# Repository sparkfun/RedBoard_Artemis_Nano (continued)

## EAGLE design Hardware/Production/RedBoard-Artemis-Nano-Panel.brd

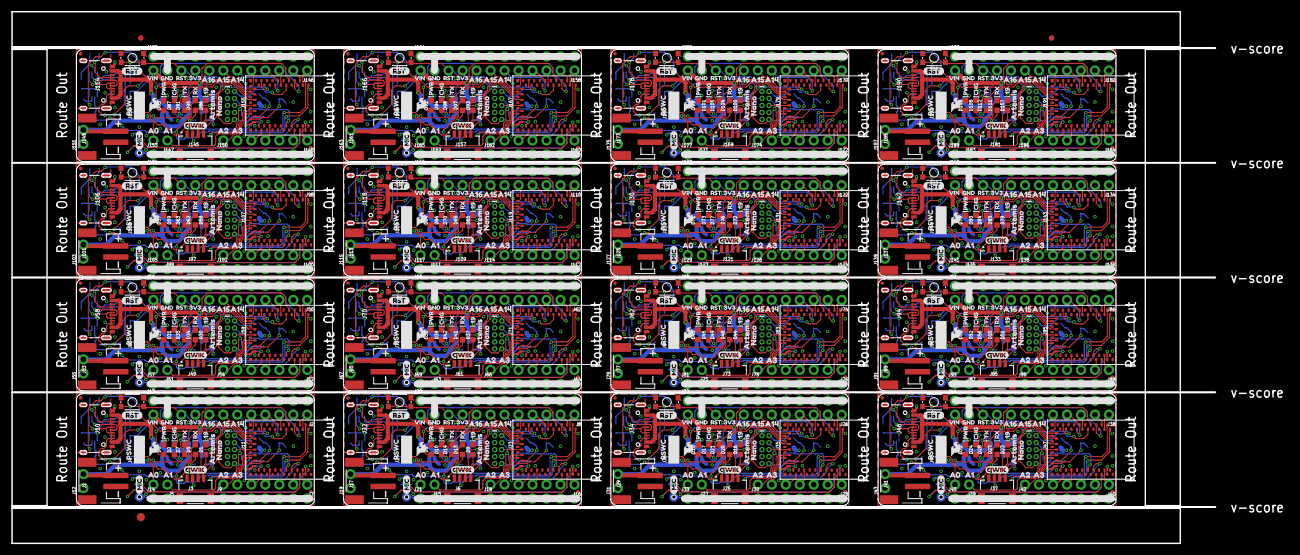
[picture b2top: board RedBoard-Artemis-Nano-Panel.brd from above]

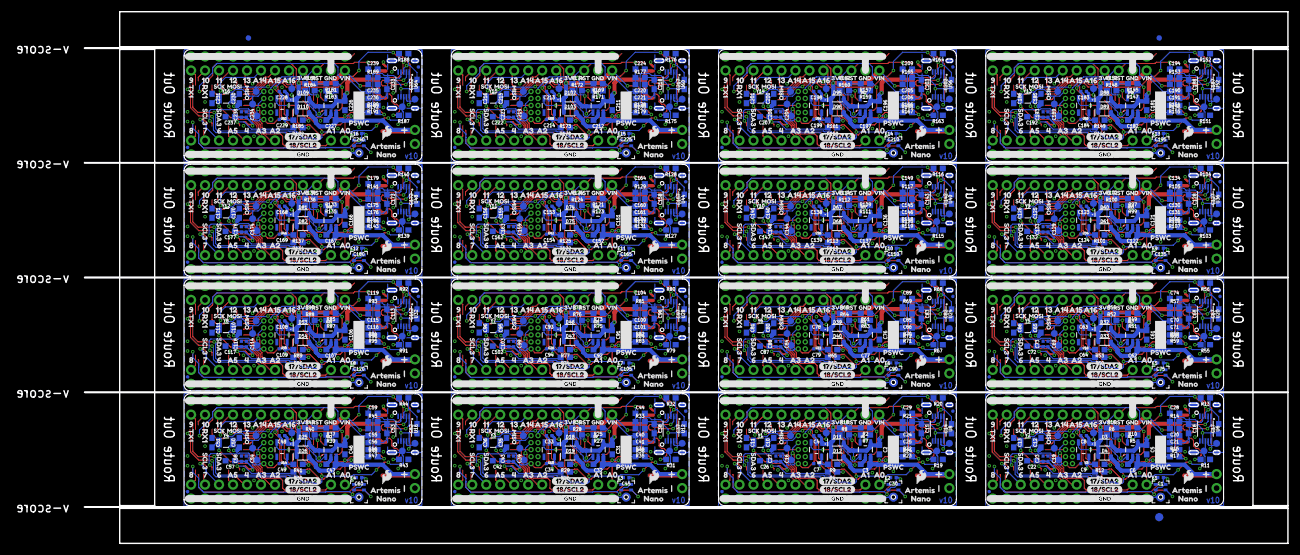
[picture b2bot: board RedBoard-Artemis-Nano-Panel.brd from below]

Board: 4 copper layers, 218.4 x 96.5 mm, 1990 parts (1267 on the bottom side), 784 nets.

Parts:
C1, C16, C19, C30, C39, C45, C54, C60, C69, C75, C84, C90, C99, C105, C114, C120, C129, C135, C144, C150, C159, C165, C174, C180, C189, C195, C204, C210, C219, C225, C234, C240: 0.1uF; 0402-TIGHT
C2, C3, C5, C6, C31, C32, C46, C47, C61, C62, C76, C77, C91, C92, C106, C107, C121, C122, C136, C137, C151, C152, C166, C167, C181, C182, C196, C197, C211, C212, C226, C227: 4.7uF; 0603
C4, C7, C8, C9, C23, C27, C33, C34, C43, C48, C49, C58, C63, C64, C73, C78, C79, C88, C93, C94, C103, C108, C109, C118, C123, C124, C133, C138, C139, C148, C153, C154, C163, C168, C169, C178, C183, C184, C193, C198, C199, C208, C213, C214, C223, C228, C229, C238: 1.0uF; 0402-TIGHT
C10, C11, C12, C13, C35, C36, C50, C51, C65, C66, C80, C81, C95, C96, C110, C111, C125, C126, C140, C141, C155, C156, C170, C171, C185, C186, C200, C201, C215, C216, C230, C231: 15pF; 0603
C14, C17, C37, C52, C67, C82, C97, C112, C127, C142, C157, C172, C187, C202, C217, C232: 10nF; 0603
C15, C18, C20, C21, C24, C25, C38, C40, C41, C53, C55, C56, C68, C70, C71, C83, C85, C86, C98, C100, C101, C113, C115, C116, C128, C130, C131, C143, C145, C146, C158, C160, C161, C173, C175, C176, C188, C190, C191, C203, C205, C206, C218, C220, C221, C233, C235, C236: 0.1uF; 0603
C22, C26, C42, C57, C72, C87, C102, C117, C132, C147, C162, C177, C192, C207, C222, C237: 10uF; 0603
C28, C29, C44, C59, C74, C89, C104, C119, C134, C149, C164, C179, C194, C209, C224, C239: 1nF; 0603
D1, D9, D16, D23, D30, D37, D44, D51, D58, D65, D72, D79, D86, D93, D100, D107: BLUE; LED-0603
D2, D5, D10, D13, D17, D20, D24, D27, D31, D34, D38, D41, D45, D48, D52, D55, D59, D62, D66, D69, D73, D76, D80, D83, D87, D90, D94, D97, D101, D104, D108, D111: Yellow; LED-0603
D3, D4, D11, D12, D18, D19, D25, D26, D32, D33, D39, D40, D46, D47, D53, D54, D60, D61, D67, D68, D74, D75, D81, D82, D88, D89, D95, D96, D102, D103, D109, D110: 1A/23V/620mV; SOD-323
D6, D8, D15, D22, D29, D36, D43, D50, D57, D64, D71, D78, D85, D92, D99, D106: RED; LED-0603
D7, D14, D21, D28, D35, D42, D49, D56, D63, D70, D77, D84, D91, D98, D105, D112: GREEN; LED-0603
E1, E2, E3, E4, E5, E6, E7, E8, E9, E10, E11, E12, E13, E14, E15, E16: SPH0641LM4H; SPH0641LM4H-1_MICROPHONE
E$1, E$2, E$3, E$4: FIDUCIAL-1X2
E$5, E$6: FIDUCIAL-1.5X3
FD1, FD2, FD3, FD4, FD5, FD6, FD7, FD8, FD9, FD10, FD11, FD12, FD13, FD14, FD15, FD16, FD17, FD18, FD19, FD20, FD21, FD22, FD23, FD24, FD25, FD26, FD27, FD28, FD29, FD30, FD31, FD32, FD33, FD34, FD35, FD36, FD37, FD38, FD39, FD40, FD41, FD42, FD43, FD44, FD45, FD46, FD47, FD48, FD49, FD50, FD51, FD52, FD53, FD54, FD55, FD56, FD57, FD58, FD59, FD60, FD61, FD62, FD63, FD64: FIDUCIALUFIDUCIAL; FIDUCIAL-MICRO
FRAME1, FRAME2, FRAME3, FRAME4, FRAME5, FRAME6, FRAME7, FRAME8, FRAME9, FRAME10, FRAME11, FRAME12, FRAME13, FRAME14, FRAME15, FRAME16: FRAME-LETTERNO_PACKAGE; DUMMY
J1, J17, J29, J41, J53, J65, J77, J89, J101, J113, J125, J137, J149, J161, J173, J185: JST-2-SMD
J2, J8, J13, J20, J26, J32, J38, J44, J50, J56, J62, J68, J74, J80, J86, J92, J98, J104, J110, J116, J122, J128, J134, J140, J146, J152, J158, J164, J170, J176, J182, J188: 1X12_NO_SILK
J3, J6, J25, J37, J49, J61, J73, J85, J97, J109, J121, J133, J145, J157, J169, J181: JST04_1MM_RA
J4, J5, J12, J14, J15, J19, J21, J24, J27, J31, J33, J36, J39, J43, J45, J48, J51, J55, J57, J60, J63, J67, J69, J72, J75, J79, J81, J84, J87, J91, J93, J96, J99, J103, J105, J108, J111, J115, J117, J120, J123, J127, J129, J132, J135, J139, J141, J144, J147, J151, J153, J156, J159, J163, J165, J168, J171, J175, J177, J180, J183, J187, J189, J192: 1X02_NO_SILK
J7, J9, J16, J18, J28, J30, J40, J42, J52, J54, J64, J66, J76, J78, J88, J90, J100, J102, J112, J114, J124, J126, J136, J138, J148, J150, J160, J162, J172, J174, J184, J186: 1X07_NO_SILK
J10, J22, J34, J46, J58, J70, J82, J94, J106, J118, J130, J142, J154, J166, J178, J190: USB Female Type C Connector; USB-C-16P-4LAYER-ISOLATED
J11, J23, J35, J47, J59, J71, J83, J95, J107, J119, J131, J143, J155, J167, J179, J191: CORTEX_DEBUG; 2X5-PTH-1.27MM-NO_SILK
LOGO1, LOGO2, LOGO3, LOGO4, LOGO5, LOGO6, LOGO7, LOGO8, LOGO9, LOGO10, LOGO11, LOGO12, LOGO13, LOGO14, LOGO15, LOGO16, LOGO17, LOGO18, LOGO19, LOGO20, LOGO21, LOGO22, LOGO23, LOGO24, LOGO25, LOGO26, LOGO27, LOGO28, LOGO29, LOGO30, LOGO31, LOGO32: SFE_LOGO_FLAME.1_INCH; SFE_LOGO_FLAME_.1
R1, R24, R36, R48, R60, R72, R84, R96, R108, R120, R132, R144, R156, R168, R180, R192: 10k; 0603
R2, R3, R4, R6, R8, R9, R10, R12, R16, R18, R25, R26, R28, R29, R30, R37, R38, R40, R41, R42, R49, R50, R52, R53, R54, R61, R62, R64, R65, R66, R73, R74, R76, R77, R78, R85, R86, R88, R89, R90, R97, R98, R100, R101, R102, R109, R110, R112, R113, R114, R121, R122, R124, R125, R126, R133, R134, R136, R137, R138, R145, R146, R148, R149, R150, R157, R158, R160, R161, R162, R169, R170, R172, R173, R174, R181, R182, R184, R185, R186: 1k; 0603
R5, R7, R27, R39, R51, R63, R75, R87, R99, R111, R123, R135, R147, R159, R171, R183: 2.0k; 0603
R11, R13, R19, R20, R31, R32, R43, R44, R55, R56, R67, R68, R79, R80, R91, R92, R103, R104, R115, R116, R127, R128, R139, R140, R151, R152, R163, R164, R175, R176, R187, R188: 5.1k; 0603
R14, R21, R33, R45, R57, R69, R81, R93, R105, R117, R129, R141, R153, R165, R177, R189: 100k; 0603
R15, R22, R34, R46, R58, R70, R82, R94, R106, R118, R130, R142, R154, R166, R178, R190: 220k; 0603
R17, R23, R35, R47, R59, R71, R83, R95, R107, R119, R131, R143, R155, R167, R179, R191: DNP; 0603
S1, S2, S3, S4, S5, S6, S7, S8, S9, S10, S11, S12, S13, S14, S15, S16: RESET; TACTILE_SWITCH_SMD_4.6X2.8MM
TP1, TP2, TP9, TP10, TP15, TP16, TP21, TP22, TP27, TP28, TP33, TP34, TP39, TP40, TP45, TP46, TP51, TP52, TP57, TP58, TP63, TP64, TP69, TP70, TP75, TP76, TP81, TP82, TP87, TP88, TP93, TP94: PAD.03X.05
TP3, TP4, TP5, TP6, TP7, TP8, TP11, TP12, TP13, TP14, TP17, TP18, TP19, TP20, TP23, TP24, TP25, TP26, TP29, TP30, TP31, TP32, TP35, TP36, TP37, TP38, TP41, TP42, TP43, TP44, TP47, TP48, TP49, TP50, TP53, TP54, TP55, TP56, TP59, TP60, TP61, TP62, TP65, TP66, TP67, TP68, TP71, TP72, TP73, TP74, TP77, TP78, TP79, TP80, TP83, TP84, TP85, TP86, TP89, TP90, TP91, TP92, TP95, TP96: TEST-POINT3X5; PAD.03X.05
U1, U7, U11, U15, U19, U23, U27, U31, U35, U39, U43, U47, U51, U55, U59, U63: ARTEMIS_MODULESMD; ARTEMIS_FP
U2, U4, U9, U13, U17, U21, U25, U29, U33, U37, U41, U45, U49, U53, U57, U61: MCP73831; SOT23-5
U3, U5, U10, U14, U18, U22, U26, U30, U34, U38, U42, U46, U50, U54, U58, U62: 3.3V; SOT23-5
U6, U8, U12, U16, U20, U24, U28, U32, U36, U40, U44, U48, U52, U56, U60, U64: CH340E_MSOP10; MSOP10
U$1, U$49, U$63, U$70, U$123, U$130, U$181, U$188, U$239, U$246, U$297, U$304, U$355, U$362, U$413, U$420, U$471, U$478, U$529, U$536, U$587, U$594, U$645, U$652, U$703, U$710, U$761, U$768, U$819, U$826, U$877, U$884: 3V316
U$2, U$80, U$140, U$198, U$256, U$314, U$372, U$430, U$488, U$546, U$604, U$662, U$720, U$778, U$836, U$894: ____GND____2
U$3, U$38, U$62, U$68, U$122, U$128, U$180, U$186, U$238, U$244, U$296, U$302, U$354, U$360, U$412, U$418, U$470, U$476, U$528, U$534, U$586, U$592, U$644, U$650, U$702, U$708, U$760, U$766, U$818, U$824, U$876, U$882: RST19
U$4, U$23, U$115, U$116, U$173, U$174, U$231, U$232, U$289, U$290, U$347, U$348, U$405, U$406, U$463, U$464, U$521, U$522, U$579, U$580, U$637, U$638, U$695, U$696, U$753, U$754, U$811, U$812, U$869, U$870, U$927, U$928: PSWC4
U$5, U$29, U$117, U$175, U$233, U$291, U$349, U$407, U$465, U$523, U$581, U$639, U$697, U$755, U$813, U$871: CHG26
U$6, U$43, U$118, U$176, U$234, U$292, U$350, U$408, U$466, U$524, U$582, U$640, U$698, U$756, U$814, U$872: PWR27
U$7, U$33, U$58, U$67, U$120, U$127, U$178, U$185, U$236, U$243, U$294, U$301, U$352, U$359, U$410, U$417, U$468, U$475, U$526, U$533, U$584, U$591, U$642, U$649, U$700, U$707, U$758, U$765, U$816, U$823, U$874, U$881: GND17
U$8, U$44, U$119, U$177, U$235, U$293, U$351, U$409, U$467, U$525, U$583, U$641, U$699, U$757, U$815, U$873: QWIIC#LOGO#JPG
U$9, U$20, U$82, U$106, U$142, U$164, U$200, U$222, U$258, U$280, U$316, U$338, U$374, U$396, U$432, U$454, U$490, U$512, U$548, U$570, U$606, U$628, U$664, U$686, U$722, U$744, U$780, U$802, U$838, U$860, U$896, U$918: A00
U$10, U$103, U$161, U$219, U$277, U$335, U$393, U$451, U$509, U$567, U$625, U$683, U$741, U$799, U$857, U$915: A57
U$11, U$100, U$158, U$216, U$274, U$332, U$390, U$448, U$506, U$564, U$622, U$680, U$738, U$796, U$854, U$912: SCL30
U$12, U$54, U$97, U$108, U$155, U$166, U$213, U$224, U$271, U$282, U$329, U$340, U$387, U$398, U$445, U$456, U$503, U$514, U$561, U$572, U$619, U$630, U$677, U$688, U$735, U$746, U$793, U$804, U$851, U$862, U$909, U$920: A145
U$13, U$22, U$71, U$77, U$131, U$137, U$189, U$195, U$247, U$253, U$305, U$311, U$363, U$369, U$421, U$427, U$479, U$485, U$537, U$543, U$595, U$601, U$653, U$659, U$711, U$717, U$769, U$775, U$827, U$833, U$885, U$891: ARTEMIS6
U$14, U$73, U$133, U$191, U$249, U$307, U$365, U$423, U$481, U$539, U$597, U$655, U$713, U$771, U$829, U$887: MISO5
U$15, U$72, U$132, U$190, U$248, U$306, U$364, U$422, U$480, U$538, U$596, U$654, U$712, U$770, U$828, U$886: MIC0
U$16, U$74, U$134, U$192, U$250, U$308, U$366, U$424, U$482, U$540, U$598, U$656, U$714, U$772, U$830, U$888: MOSI4
U$17, U$24, U$75, U$78, U$135, U$138, U$193, U$196, U$251, U$254, U$309, U$312, U$367, U$370, U$425, U$428, U$483, U$486, U$541, U$544, U$599, U$602, U$657, U$660, U$715, U$718, U$773, U$776, U$831, U$834, U$889, U$892: NANO7
U$18, U$76, U$136, U$194, U$252, U$310, U$368, U$426, U$484, U$542, U$600, U$658, U$716, U$774, U$832, U$890: SCK3
U$19, U$42, U$91, U$104, U$149, U$162, U$207, U$220, U$265, U$278, U$323, U$336, U$381, U$394, U$439, U$452, U$497, U$510, U$555, U$568, U$613, U$626, U$671, U$684, U$729, U$742, U$787, U$800, U$845, U$858, U$903, U$916: A32
U$21, U$41, U$90, U$105, U$148, U$163, U$206, U$221, U$264, U$279, U$322, U$337, U$380, U$395, U$438, U$453, U$496, U$511, U$554, U$569, U$612, U$627, U$670, U$685, U$728, U$743, U$786, U$801, U$844, U$859, U$902, U$917: A21
U$25, U$81, U$141, U$199, U$257, U$315, U$373, U$431, U$489, U$547, U$605, U$663, U$721, U$779, U$837, U$895: PRODUCTION_INSTRUCTIONS
U$26, U$114, U$172, U$230, U$288, U$346, U$404, U$462, U$520, U$578, U$636, U$694, U$752, U$810, U$868, U$926: 191
U$27, U$39, U$61, U$69, U$121, U$129, U$179, U$187, U$237, U$245, U$295, U$303, U$353, U$361, U$411, U$419, U$469, U$477, U$527, U$535, U$585, U$593, U$643, U$651, U$701, U$709, U$759, U$767, U$817, U$825, U$875, U$883: VIN19
U$28, U$55, U$98, U$109, U$156, U$167, U$214, U$225, U$272, U$283, U$330, U$341, U$388, U$399, U$446, U$457, U$504, U$515, U$562, U$573, U$620, U$631, U$678, U$689, U$736, U$747, U$794, U$805, U$852, U$863, U$910, U$921: A156
U$30, U$79, U$139, U$197, U$255, U$313, U$371, U$429, U$487, U$545, U$603, U$661, U$719, U$777, U$835, U$893: GND2
U$31, U$101, U$159, U$217, U$275, U$333, U$391, U$449, U$507, U$565, U$623, U$681, U$739, U$797, U$855, U$913: SDA31
U$32, U$83, U$143, U$201, U$259, U$317, U$375, U$433, U$491, U$549, U$607, U$665, U$723, U$781, U$839, U$897: 46
U$34, U$40, U$89, U$107, U$147, U$165, U$205, U$223, U$263, U$281, U$321, U$339, U$379, U$397, U$437, U$455, U$495, U$513, U$553, U$571, U$611, U$629, U$669, U$687, U$727, U$745, U$785, U$803, U$843, U$861, U$901, U$919: A10
U$35, U$84, U$144, U$202, U$260, U$318, U$376, U$434, U$492, U$550, U$608, U$666, U$724, U$782, U$840, U$898: 68
U$36, U$87, U$145, U$203, U$261, U$319, U$377, U$435, U$493, U$551, U$609, U$667, U$725, U$783, U$841, U$899: 79
U$37, U$88, U$146, U$204, U$262, U$320, U$378, U$436, U$494, U$552, U$610, U$668, U$726, U$784, U$842, U$900: 810
U$45, U$92, U$150, U$208, U$266, U$324, U$382, U$440, U$498, U$556, U$614, U$672, U$730, U$788, U$846, U$904: 90
U$46, U$93, U$151, U$209, U$267, U$325, U$383, U$441, U$499, U$557, U$615, U$673, U$731, U$789, U$847, U$905: 101
U$47, U$94, U$152, U$210, U$268, U$326, U$384, U$442, U$500, U$558, U$616, U$674, U$732, U$790, U$848, U$906: 112
U$48, U$56, U$99, U$110, U$157, U$168, U$215, U$226, U$273, U$284, U$331, U$342, U$389, U$400, U$447, U$458, U$505, U$516, U$563, U$574, U$621, U$632, U$679, U$690, U$737, U$748, U$795, U$806, U$853, U$864, U$911, U$922: A167
U$50, U$111, U$169, U$227, U$285, U$343, U$401, U$459, U$517, U$575, U$633, U$691, U$749, U$807, U$865, U$923: RX10
U$51, U$64, U$124, U$182, U$240, U$298, U$356, U$414, U$472, U$530, U$588, U$646, U$704, U$762, U$820, U$878: RST1
U$52, U$95, U$153, U$211, U$269, U$327, U$385, U$443, U$501, U$559, U$617, U$675, U$733, U$791, U$849, U$907: 123
U$53, U$96, U$154, U$212, U$270, U$328, U$386, U$444, U$502, U$560, U$618, U$676, U$734, U$792, U$850, U$908: 134
U$57, U$112, U$170, U$228, U$286, U$344, U$402, U$460, U$518, U$576, U$634, U$692, U$750, U$808, U$866, U$924: 17#SDA21
U$59, U$102, U$160, U$218, U$276, U$334, U$392, U$450, U$508, U$566, U$624, U$682, U$740, U$798, U$856, U$914: TX12
U$60, U$113, U$171, U$229, U$287, U$345, U$403, U$461, U$519, U$577, U$635, U$693, U$751, U$809, U$867, U$925: 18#SCL20
U$65, U$85, U$125, U$183, U$241, U$299, U$357, U$415, U$473, U$531, U$589, U$647, U$705, U$763, U$821, U$879: RX23
U$66, U$86, U$126, U$184, U$242, U$300, U$358, U$416, U$474, U$532, U$590, U$648, U$706, U$764, U$822, U$880: TX22
Y1, Y2, Y3, Y4, Y5, Y6, Y7, Y8, Y9, Y10, Y11, Y12, Y13, Y14, Y15, Y16: 32.768kHz; CRYSTAL-SMD-3.2X1.5MM

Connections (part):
1: J16.1, U7.D38
2: J8.2, U7.D40
3: J28.1, U11.D38
3.3V: C1.1, C9.1, C17.1, C18.1, C19.2, C22.1, C23.1, E1.2, E1.5, J2.9, J3.2, J11.1, R10.2, R12.2, R14.2, R16.2, U1.VDD@36, U1.VDD@37, U3.5, U6.7, U6.10
3.3V1: C7.1, C14.1, C15.1, C16.2, C26.1, C27.1, C30.1, E2.2, E2.5, J6.2, J8.9, J23.1, R2.2, R9.2, R18.2, R21.2, U5.5, U7.VDD@36, U7.VDD@37, U8.7, U8.10
3.3V2: C34.1, C37.1, C38.1, C39.2, C42.1, C43.1, C45.1, E3.2, E3.5, J25.2, J26.9, J35.1, R25.2, R29.2, R30.2, R33.2, U10.5, U11.VDD@36, U11.VDD@37, U12.7, U12.10
3.3V3: C49.1, C52.1, C53.1, C54.2, C57.1, C58.1, C60.1, E4.2, E4.5, J37.2, J38.9, J47.1, R37.2, R41.2, R42.2, R45.2, U14.5, U15.VDD@36, U15.VDD@37, U16.7, U16.10
3.3V4: C64.1, C67.1, C68.1, C69.2, C72.1, C73.1, C75.1, E5.2, E5.5, J49.2, J50.9, J59.1, R49.2, R53.2, R54.2, R57.2, U18.5, U19.VDD@36, U19.VDD@37, U20.7, U20.10
3.3V5: C79.1, C82.1, C83.1, C84.2, C87.1, C88.1, C90.1, E6.2, E6.5, J61.2, J62.9, J71.1, R61.2, R65.2, R66.2, R69.2, U22.5, U23.VDD@36, U23.VDD@37, U24.7, U24.10
3.3V6: C94.1, C97.1, C98.1, C99.2, C102.1, C103.1, C105.1, E7.2, E7.5, J73.2, J74.9, J83.1, R73.2, R77.2, R78.2, R81.2, U26.5, U27.VDD@36, U27.VDD@37, U28.7, U28.10
3.3V7: C109.1, C112.1, C113.1, C114.2, C117.1, C118.1, C120.1, E8.2, E8.5, J85.2, J86.9, J95.1, R85.2, R89.2, R90.2, R93.2, U30.5, U31.VDD@36, U31.VDD@37, U32.7, U32.10
3.3V8: C124.1, C127.1, C128.1, C129.2, C132.1, C133.1, C135.1, E9.2, E9.5, J97.2, J98.9, J107.1, R97.2, R101.2, R102.2, R105.2, U34.5, U35.VDD@36, U35.VDD@37, U36.7, U36.10
3.3V9: C139.1, C142.1, C143.1, C144.2, C147.1, C148.1, C150.1, E10.2, E10.5, J109.2, J110.9, J119.1, R109.2, R113.2, R114.2, R117.2, U38.5, U39.VDD@36, U39.VDD@37, U40.7, U40.10
3.3V10: C154.1, C157.1, C158.1, C159.2, C162.1, C163.1, C165.1, E11.2, E11.5, J121.2, J122.9, J131.1, R121.2, R125.2, R126.2, R129.2, U42.5, U43.VDD@36, U43.VDD@37, U44.7, U44.10
3.3V11: C169.1, C172.1, C173.1, C174.2, C177.1, C178.1, C180.1, E12.2, E12.5, J133.2, J134.9, J143.1, R133.2, R137.2, R138.2, R141.2, U46.5, U47.VDD@36, U47.VDD@37, U48.7, U48.10
3.3V12: C184.1, C187.1, C188.1, C189.2, C192.1, C193.1, C195.1, E13.2, E13.5, J145.2, J146.9, J155.1, R145.2, R149.2, R150.2, R153.2, U50.5, U51.VDD@36, U51.VDD@37, U52.7, U52.10
3.3V13: C199.1, C202.1, C203.1, C204.2, C207.1, C208.1, C210.1, E14.2, E14.5, J157.2, J158.9, J167.1, R157.2, R161.2, R162.2, R165.2, U54.5, U55.VDD@36, U55.VDD@37, U56.7, U56.10
3.3V14: C214.1, C217.1, C218.1, C219.2, C222.1, C223.1, C225.1, E15.2, E15.5, J169.2, J170.9, J179.1, R169.2, R173.2, R174.2, R177.2, U58.5, U59.VDD@36, U59.VDD@37, U60.7, U60.10
3.3V15: C229.1, C232.1, C233.1, C234.2, C237.1, C238.1, C240.1, E16.2, E16.5, J181.2, J182.9, J191.1, R181.2, R185.2, R186.2, R189.2, U62.5, U63.VDD@36, U63.VDD@37, U64.7, U64.10
4: J26.2, U11.D40
5: J40.1, U15.D38
6: J38.2, U15.D40
7: J52.1, U19.D38
8: J7.1, U1.D38
9: J50.2, U19.D40
10: J2.2, U1.D40
11: J64.1, U23.D38
12: J62.2, U23.D40
13: J76.1, U27.D38
14: J74.2, U27.D40
15: J88.1, U31.D38
16: J86.2, U31.D40
17: J100.1, U35.D38
18: J98.2, U35.D40
19: J112.1, U39.D38
20: J110.2, U39.D40
21: J124.1, U43.D38
22: J122.2, U43.D40
23: J136.1, U47.D38
24: J134.2, U47.D40
25: J148.1, U51.D38
26: J146.2, U51.D40
27: J160.1, U55.D38
28: J158.2, U55.D40
29: J172.1, U59.D38
30: J170.2, U59.D40
31: J184.1, U63.D38
32: J182.2, U63.D40
!RESET: C20.2, C28.1, J2.10, J11.10, R14.1, S1.3, S1.4, U1.~RST
!RESET1: C24.2, C29.1, J8.10, J23.10, R21.1, S2.3, S2.4, U7.~RST
!RESET2: C40.2, C44.1, J26.10, J35.10, R33.1, S3.3, S3.4, U11.~RST
!RESET3: C55.2, C59.1, J38.10, J47.10, R45.1, S4.3, S4.4, U15.~RST
!RESET4: C70.2, C74.1, J50.10, J59.10, R57.1, S5.3, S5.4, U19.~RST
!RESET5: C85.2, C89.1, J62.10, J71.10, R69.1, S6.3, S6.4, U23.~RST
!RESET6: C100.2, C104.1, J74.10, J83.10, R81.1, S7.3, S7.4, U27.~RST
!RESET7: C115.2, C119.1, J86.10, J95.10, R93.1, S8.3, S8.4, U31.~RST
!RESET8: C130.2, C134.1, J98.10, J107.10, R105.1, S9.3, S9.4, U35.~RST
!RESET9: C145.2, C149.1, J110.10, J119.10, R117.1, S10.3, S10.4, U39.~RST
!RESET10: C160.2, C164.1, J122.10, J131.10, R129.1, S11.3, S11.4, U43.~RST
!RESET11: C175.2, C179.1, J134.10, J143.10, R141.1, S12.3, S12.4, U47.~RST
!RESET12: C190.2, C194.1, J146.10, J155.10, R153.1, S13.3, S13.4, U51.~RST
!RESET13: C205.2, C209.1, J158.10, J167.10, R165.1, S14.3, S14.4, U55.~RST
!RESET14: C220.2, C224.1, J170.10, J179.10, R177.1, S15.3, S15.4, U59.~RST
!RESET15: C235.2, C239.1, J182.10, J191.10, R189.1, S16.3, S16.4, U63.~RST
!RTS: C20.1, C21.1, R17.2, U6.4
!RTS1: C24.1, C25.1, R23.2, U8.4
!RTS2: C40.1, C41.1, R35.2, U12.4
!RTS3: C55.1, C56.1, R47.2, U16.4
!RTS4: C70.1, C71.1, R59.2, U20.4
!RTS5: C85.1, C86.1, R71.2, U24.4
!RTS6: C100.1, C101.1, R83.2, U28.4
!RTS7: C115.1, C116.1, R95.2, U32.4
!RTS8: C130.1, C131.1, R107.2, U36.4
!RTS9: C145.1, C146.1, R119.2, U40.4
!RTS10: C160.1, C161.1, R131.2, U44.4
!RTS11: C175.1, C176.1, R143.2, U48.4
!RTS12: C190.1, C191.1, R155.2, U52.4
!RTS13: C205.1, C206.1, R167.2, U56.4
!RTS14: C220.1, C221.1, R179.2, U60.4
!RTS15: C235.1, C236.1, R191.2, U64.4
BOOT: C21.2, R15.2, U1.BOOT
BOOT1: C25.2, R22.2, U7.BOOT
BOOT2: C41.2, R34.2, U11.BOOT
BOOT3: C56.2, R46.2, U15.BOOT
BOOT4: C71.2, R58.2, U19.BOOT
BOOT5: C86.2, R70.2, U23.BOOT
BOOT6: C101.2, R82.2, U27.BOOT
BOOT7: C116.2, R94.2, U31.BOOT
BOOT8: C131.2, R106.2, U35.BOOT
BOOT9: C146.2, R118.2, U39.BOOT
BOOT10: C161.2, R130.2, U43.BOOT
BOOT11: C176.2, R142.2, U47.BOOT
BOOT12: C191.2, R154.2, U51.BOOT
BOOT13: C206.2, R166.2, U55.BOOT
BOOT14: C221.2, R178.2, U59.BOOT
BOOT15: C236.2, R190.2, U63.BOOT
CC1: J10.A5, R13.2
CC2: J10.B5, R11.2
CC3: J22.B5, R19.2
CC4: J22.A5, R20.2
CC5: J34.B5, R31.2
CC6: J34.A5, R32.2
CC7: J46.B5, R43.2
CC8: J46.A5, R44.2
CC9: J58.B5, R55.2
CC10: J58.A5, R56.2
CC11: J70.B5, R67.2
CC12: J70.A5, R68.2
CC13: J82.B5, R79.2
CC14: J82.A5, R80.2
CC15: J94.B5, R91.2
CC16: J94.A5, R92.2
CC17: J106.B5, R103.2
CC18: J106.A5, R104.2
CC19: J118.B5, R115.2
CC20: J118.A5, R116.2
CC21: J130.B5, R127.2
CC22: J130.A5, R128.2
CC23: J142.B5, R139.2
CC24: J142.A5, R140.2
CC25: J154.B5, R151.2
CC26: J154.A5, R152.2
CC27: J166.B5, R163.2
CC28: J166.A5, R164.2
CC29: J178.B5, R175.2
CC30: J178.A5, R176.2
CC31: J190.B5, R187.2
CC32: J190.A5, R188.2
D+1: J10.A6, J10.B6, U6.1
D+2: J22.A6, J22.B6, U8.1
D+3: J34.A6, J34.B6, U12.1
D+4: J46.A6, J46.B6, U16.1
D+5: J58.A6, J58.B6, U20.1
D+6: J70.A6, J70.B6, U24.1
D+7: J82.A6, J82.B6, U28.1
D+8: J94.A6, J94.B6, U32.1
D+9: J106.A6, J106.B6, U36.1
D+10: J118.A6, J118.B6, U40.1
D+11: J130.A6, J130.B6, U44.1
D+12: J142.A6, J142.B6, U48.1
D+13: J154.A6, J154.B6, U52.1
D+14: J166.A6, J166.B6, U56.1
D+15: J178.A6, J178.B6, U60.1
D+16: J190.A6, J190.B6, U64.1
D-1: J10.A7, J10.B7, U6.2
D-2: J22.A7, J22.B7, U8.2
D-3: J34.A7, J34.B7, U12.2
D-4: J46.A7, J46.B7, U16.2
D-5: J58.A7, J58.B7, U20.2
D-6: J70.A7, J70.B7, U24.2
D-7: J82.A7, J82.B7, U28.2
D-8: J94.A7, J94.B7, U32.2
D-9: J106.A7, J106.B7, U36.2
D-10: J118.A7, J118.B7, U40.2
D-11: J130.A7, J130.B7, U44.2
D-12: J142.A7, J142.B7, U48.2
D-13: J154.A7, J154.B7, U52.2
D-14: J166.A7, J166.B7, U56.2
D-15: J178.A7, J178.B7, U60.2
D-16: J190.A7, J190.B7, U64.2
GND: C1.2, C5.2, C6.2, C8.2, C9.2, C12.1, C13.1, C17.2, C18.2, C19.1, C22.2, C23.2, C28.2, D1.C, D6.C, E1.3, E1.6, E1.7, E1.8, J1.1, J2.11, J3.1, J4.2, J9.1, J9.2, J9.3, J9.4, J9.5, J9.6, J9.7, J10.GND, J10.GND2, J11.3, J11.5, J11.9, J12.1, J13.1, J13.2, J13.3, J13.4, J13.5, J13.6, J13.7, J13.8, J13.9, J13.10, J13.11, J13.12, J14.1, J14.2, R5.1, R11.1, R13.1, R15.1, R17.1, S1.1, S1.2, U1.GND@1, U1.GND@22, U1.GND@38, U1.GND@39, U1.GND@47, U1.GND@59, U2.2, U3.2, U6.3
GND1: C2.2, C3.2, C4.2, C7.2, C10.1, C11.1, C14.2, C15.2, C16.1, C26.2, C27.2, C29.2, C30.2, D8.C, D9.C, E2.3, E2.6, E2.7, E2.8, J6.1, J8.11, J17.1, J18.1, J18.2, J18.3, J18.4, J18.5, J18.6, J18.7, J19.1, J20.1, J20.2, J20.3, J20.4, J20.5, J20.6, J20.7, J20.8, J20.9, J20.10, J20.11, J20.12, J21.1, J21.2, J22.GND, J22.GND2, J23.3, J23.5, J23.9, J24.2, R7.1, R19.1, R20.1, R22.1, R23.1, S2.1, S2.2, U4.2, U5.2, U7.GND@1, U7.GND@22, U7.GND@38, U7.GND@39, U7.GND@47, U7.GND@59, U8.3
GND2: C31.2, C32.2, C33.2, C34.2, C35.1, C36.1, C37.2, C38.2, C39.1, C42.2, C43.2, C44.2, C45.2, D15.C, D16.C, E3.3, E3.6, E3.7, E3.8, J25.1, J26.11, J29.1, J30.1, J30.2, J30.3, J30.4, J30.5, J30.6, J30.7, J31.1, J32.1, J32.2, J32.3, J32.4, J32.5, J32.6, J32.7, J32.8, J32.9, J32.10, J32.11, J32.12, J33.1, J33.2, J34.GND, J34.GND2, J35.3, J35.5, J35.9, J36.2, R27.1, R31.1, R32.1, R34.1, R35.1, S3.1, S3.2, U9.2, U10.2, U11.GND@1, U11.GND@22, U11.GND@38, U11.GND@39, U11.GND@47, U11.GND@59, U12.3
GND3: C46.2, C47.2, C48.2, C49.2, C50.1, C51.1, C52.2, C53.2, C54.1, C57.2, C58.2, C59.2, C60.2, D22.C, D23.C, E4.3, E4.6, E4.7, E4.8, J37.1, J38.11, J41.1, J42.1, J42.2, J42.3, J42.4, J42.5, J42.6, J42.7, J43.1, J44.1, J44.2, J44.3, J44.4, J44.5, J44.6, J44.7, J44.8, J44.9, J44.10, J44.11, J44.12, J45.1, J45.2, J46.GND, J46.GND2, J47.3, J47.5, J47.9, J48.2, R39.1, R43.1, R44.1, R46.1, R47.1, S4.1, S4.2, U13.2, U14.2, U15.GND@1, U15.GND@22, U15.GND@38, U15.GND@39, U15.GND@47, U15.GND@59, U16.3
GND4: C61.2, C62.2, C63.2, C64.2, C65.1, C66.1, C67.2, C68.2, C69.1, C72.2, C73.2, C74.2, C75.2, D29.C, D30.C, E5.3, E5.6, E5.7, E5.8, J49.1, J50.11, J53.1, J54.1, J54.2, J54.3, J54.4, J54.5, J54.6, J54.7, J55.1, J56.1, J56.2, J56.3, J56.4, J56.5, J56.6, J56.7, J56.8, J56.9, J56.10, J56.11, J56.12, J57.1, J57.2, J58.GND, J58.GND2, J59.3, J59.5, J59.9, J60.2, R51.1, R55.1, R56.1, R58.1, R59.1, S5.1, S5.2, U17.2, U18.2, U19.GND@1, U19.GND@22, U19.GND@38, U19.GND@39, U19.GND@47, U19.GND@59, U20.3
GND5: C76.2, C77.2, C78.2, C79.2, C80.1, C81.1, C82.2, C83.2, C84.1, C87.2, C88.2, C89.2, C90.2, D36.C, D37.C, E6.3, E6.6, E6.7, E6.8, J61.1, J62.11, J65.1, J66.1, J66.2, J66.3, J66.4, J66.5, J66.6, J66.7, J67.1, J68.1, J68.2, J68.3, J68.4, J68.5, J68.6, J68.7, J68.8, J68.9, J68.10, J68.11, J68.12, J69.1, J69.2, J70.GND, J70.GND2, J71.3, J71.5, J71.9, J72.2, R63.1, R67.1, R68.1, R70.1, R71.1, S6.1, S6.2, U21.2, U22.2, U23.GND@1, U23.GND@22, U23.GND@38, U23.GND@39, U23.GND@47, U23.GND@59, U24.3
GND6: C91.2, C92.2, C93.2, C94.2, C95.1, C96.1, C97.2, C98.2, C99.1, C102.2, C103.2, C104.2, C105.2, D43.C, D44.C, E7.3, E7.6, E7.7, E7.8, J73.1, J74.11, J77.1, J78.1, J78.2, J78.3, J78.4, J78.5, J78.6, J78.7, J79.1, J80.1, J80.2, J80.3, J80.4, J80.5, J80.6, J80.7, J80.8, J80.9, J80.10, J80.11, J80.12, J81.1, J81.2, J82.GND, J82.GND2, J83.3, J83.5, J83.9, J84.2, R75.1, R79.1, R80.1, R82.1, R83.1, S7.1, S7.2, U25.2, U26.2, U27.GND@1, U27.GND@22, U27.GND@38, U27.GND@39, U27.GND@47, U27.GND@59, U28.3
GND7: C106.2, C107.2, C108.2, C109.2, C110.1, C111.1, C112.2, C113.2, C114.1, C117.2, C118.2, C119.2, C120.2, D50.C, D51.C, E8.3, E8.6, E8.7, E8.8, J85.1, J86.11, J89.1, J90.1, J90.2, J90.3, J90.4, J90.5, J90.6, J90.7, J91.1, J92.1, J92.2, J92.3, J92.4, J92.5, J92.6, J92.7, J92.8, J92.9, J92.10, J92.11, J92.12, J93.1, J93.2, J94.GND, J94.GND2, J95.3, J95.5, J95.9, J96.2, R87.1, R91.1, R92.1, R94.1, R95.1, S8.1, S8.2, U29.2, U30.2, U31.GND@1, U31.GND@22, U31.GND@38, U31.GND@39, U31.GND@47, U31.GND@59, U32.3
GND8: C121.2, C122.2, C123.2, C124.2, C125.1, C126.1, C127.2, C128.2, C129.1, C132.2, C133.2, C134.2, C135.2, D57.C, D58.C, E9.3, E9.6, E9.7, E9.8, J97.1, J98.11, J101.1, J102.1, J102.2, J102.3, J102.4, J102.5, J102.6, J102.7, J103.1, J104.1, J104.2, J104.3, J104.4, J104.5, J104.6, J104.7, J104.8, J104.9, J104.10, J104.11, J104.12, J105.1, J105.2, J106.GND, J106.GND2, J107.3, J107.5, J107.9, J108.2, R99.1, R103.1, R104.1, R106.1, R107.1, S9.1, S9.2, U33.2, U34.2, U35.GND@1, U35.GND@22, U35.GND@38, U35.GND@39, U35.GND@47, U35.GND@59, U36.3
GND9: C136.2, C137.2, C138.2, C139.2, C140.1, C141.1, C142.2, C143.2, C144.1, C147.2, C148.2, C149.2, C150.2, D64.C, D65.C, E10.3, E10.6, E10.7, E10.8, J109.1, J110.11, J113.1, J114.1, J114.2, J114.3, J114.4, J114.5, J114.6, J114.7, J115.1, J116.1, J116.2, J116.3, J116.4, J116.5, J116.6, J116.7, J116.8, J116.9, J116.10, J116.11, J116.12, J117.1, J117.2, J118.GND, J118.GND2, J119.3, J119.5, J119.9, J120.2, R111.1, R115.1, R116.1, R118.1, R119.1, S10.1, S10.2, U37.2, U38.2, U39.GND@1, U39.GND@22, U39.GND@38, U39.GND@39, U39.GND@47, U39.GND@59, U40.3
GND10: C151.2, C152.2, C153.2, C154.2, C155.1, C156.1, C157.2, C158.2, C159.1, C162.2, C163.2, C164.2, C165.2, D71.C, D72.C, E11.3, E11.6, E11.7, E11.8, J121.1, J122.11, J125.1, J126.1, J126.2, J126.3, J126.4, J126.5, J126.6, J126.7, J127.1, J128.1, J128.2, J128.3, J128.4, J128.5, J128.6, J128.7, J128.8, J128.9, J128.10, J128.11, J128.12, J129.1, J129.2, J130.GND, J130.GND2, J131.3, J131.5, J131.9, J132.2, R123.1, R127.1, R128.1, R130.1, R131.1, S11.1, S11.2, U41.2, U42.2, U43.GND@1, U43.GND@22, U43.GND@38, U43.GND@39, U43.GND@47, U43.GND@59, U44.3
GND11: C166.2, C167.2, C168.2, C169.2, C170.1, C171.1, C172.2, C173.2, C174.1, C177.2, C178.2, C179.2, C180.2, D78.C, D79.C, E12.3, E12.6, E12.7, E12.8, J133.1, J134.11, J137.1, J138.1, J138.2, J138.3, J138.4, J138.5, J138.6, J138.7, J139.1, J140.1, J140.2, J140.3, J140.4, J140.5, J140.6, J140.7, J140.8, J140.9, J140.10, J140.11, J140.12, J141.1, J141.2, J142.GND, J142.GND2, J143.3, J143.5, J143.9, J144.2, R135.1, R139.1, R140.1, R142.1, R143.1, S12.1, S12.2, U45.2, U46.2, U47.GND@1, U47.GND@22, U47.GND@38, U47.GND@39, U47.GND@47, U47.GND@59, U48.3
GND12: C181.2, C182.2, C183.2, C184.2, C185.1, C186.1, C187.2, C188.2, C189.1, C192.2, C193.2, C194.2, C195.2, D85.C, D86.C, E13.3, E13.6, E13.7, E13.8, J145.1, J146.11, J149.1, J150.1, J150.2, J150.3, J150.4, J150.5, J150.6, J150.7, J151.1, J152.1, J152.2, J152.3, J152.4, J152.5, J152.6, J152.7, J152.8, J152.9, J152.10, J152.11, J152.12, J153.1, J153.2, J154.GND, J154.GND2, J155.3, J155.5, J155.9, J156.2, R147.1, R151.1, R152.1, R154.1, R155.1, S13.1, S13.2, U49.2, U50.2, U51.GND@1, U51.GND@22, U51.GND@38, U51.GND@39, U51.GND@47, U51.GND@59, U52.3
GND13: C196.2, C197.2, C198.2, C199.2, C200.1, C201.1, C202.2, C203.2, C204.1, C207.2, C208.2, C209.2, C210.2, D92.C, D93.C, E14.3, E14.6, E14.7, E14.8, J157.1, J158.11, J161.1, J162.1, J162.2, J162.3, J162.4, J162.5, J162.6, J162.7, J163.1, J164.1, J164.2, J164.3, J164.4, J164.5, J164.6, J164.7, J164.8, J164.9, J164.10, J164.11, J164.12, J165.1, J165.2, J166.GND, J166.GND2, J167.3, J167.5, J167.9, J168.2, R159.1, R163.1, R164.1, R166.1, R167.1, S14.1, S14.2, U53.2, U54.2, U55.GND@1, U55.GND@22, U55.GND@38, U55.GND@39, U55.GND@47, U55.GND@59, U56.3
GND14: C211.2, C212.2, C213.2, C214.2, C215.1, C216.1, C217.2, C218.2, C219.1, C222.2, C223.2, C224.2, C225.2, D99.C, D100.C, E15.3, E15.6, E15.7, E15.8, J169.1, J170.11, J173.1, J174.1, J174.2, J174.3, J174.4, J174.5, J174.6, J174.7, J175.1, J176.1, J176.2, J176.3, J176.4, J176.5, J176.6, J176.7, J176.8, J176.9, J176.10, J176.11, J176.12, J177.1, J177.2, J178.GND, J178.GND2, J179.3, J179.5, J179.9, J180.2, R171.1, R175.1, R176.1, R178.1, R179.1, S15.1, S15.2, U57.2, U58.2, U59.GND@1, U59.GND@22, U59.GND@38, U59.GND@39, U59.GND@47, U59.GND@59, U60.3
GND15: C226.2, C227.2, C228.2, C229.2, C230.1, C231.1, C232.2, C233.2, C234.1, C237.2, C238.2, C239.2, C240.2, D106.C, D107.C, E16.3, E16.6, E16.7, E16.8, J181.1, J182.11, J185.1, J186.1, J186.2, J186.3, J186.4, J186.5, J186.6, J186.7, J187.1, J188.1, J188.2, J188.3, J188.4, J188.5, J188.6, J188.7, J188.8, J188.9, J188.10, J188.11, J188.12, J189.1, J189.2, J190.GND, J190.GND2, J191.3, J191.5, J191.9, J192.2, R183.1, R187.1, R188.1, R190.1, R191.1, S16.1, S16.2, U61.2, U62.2, U63.GND@1, U63.GND@22, U63.GND@38, U63.GND@39, U63.GND@47, U63.GND@59, U64.3
unnamed: R5.2, U2.5
unnamed: C12.2, U1.XO, Y2.P$2
unnamed: D2.C, R6.2
unnamed: R6.1, U2.1
unnamed: D7.A, R16.1
unnamed: D8.A, R2.1
unnamed: D1.A, R3.1
unnamed: C13.2, U1.XI, Y2.P$1
unnamed: D5.A, R12.1
unnamed: D6.A, R10.1
unnamed: D9.A, R4.1
unnamed: R7.2, U4.5
unnamed: D10.C, R8.2
unnamed: R8.1, U4.1
unnamed: C10.2, U7.XO, Y1.P$2
unnamed: C11.2, U7.XI, Y1.P$1
unnamed: D14.A, R18.1
unnamed: D13.A, R9.1
unnamed: D15.A, R25.1
unnamed: D16.A, R26.1
unnamed: R27.2, U9.5
unnamed: D17.C, R28.2
unnamed: R28.1, U9.1
unnamed: C35.2, U11.XO, Y3.P$2
unnamed: C36.2, U11.XI, Y3.P$1
unnamed: D21.A, R30.1
unnamed: D20.A, R29.1
unnamed: D22.A, R37.1
unnamed: D23.A, R38.1
unnamed: R39.2, U13.5
unnamed: D24.C, R40.2
unnamed: R40.1, U13.1
unnamed: C50.2, U15.XO, Y4.P$2
unnamed: C51.2, U15.XI, Y4.P$1
unnamed: D28.A, R42.1
unnamed: D27.A, R41.1
unnamed: D29.A, R49.1
unnamed: D30.A, R50.1
unnamed: R51.2, U17.5
unnamed: D31.C, R52.2
unnamed: R52.1, U17.1
unnamed: C65.2, U19.XO, Y5.P$2
unnamed: C66.2, U19.XI, Y5.P$1
unnamed: D35.A, R54.1
unnamed: D34.A, R53.1
unnamed: D36.A, R61.1
unnamed: D37.A, R62.1
unnamed: R63.2, U21.5
unnamed: D38.C, R64.2
unnamed: R64.1, U21.1
unnamed: C80.2, U23.XO, Y6.P$2
unnamed: C81.2, U23.XI, Y6.P$1
unnamed: D42.A, R66.1
unnamed: D41.A, R65.1
unnamed: D43.A, R73.1
unnamed: D44.A, R74.1
unnamed: R75.2, U25.5
unnamed: D45.C, R76.2
unnamed: R76.1, U25.1
unnamed: C95.2, U27.XO, Y7.P$2
unnamed: C96.2, U27.XI, Y7.P$1
unnamed: D49.A, R78.1
unnamed: D48.A, R77.1
unnamed: D50.A, R85.1
unnamed: D51.A, R86.1
unnamed: R87.2, U29.5
unnamed: D52.C, R88.2
unnamed: R88.1, U29.1
unnamed: C110.2, U31.XO, Y8.P$2
unnamed: C111.2, U31.XI, Y8.P$1
unnamed: D56.A, R90.1
unnamed: D55.A, R89.1
unnamed: D57.A, R97.1
unnamed: D58.A, R98.1
unnamed: R99.2, U33.5
unnamed: D59.C, R100.2
unnamed: R100.1, U33.1
unnamed: C125.2, U35.XO, Y9.P$2
unnamed: C126.2, U35.XI, Y9.P$1
unnamed: D63.A, R102.1
unnamed: D62.A, R101.1
unnamed: D64.A, R109.1
unnamed: D65.A, R110.1
unnamed: R111.2, U37.5
unnamed: D66.C, R112.2
unnamed: R112.1, U37.1
unnamed: C140.2, U39.XO, Y10.P$2
unnamed: C141.2, U39.XI, Y10.P$1
unnamed: D70.A, R114.1
unnamed: D69.A, R113.1
unnamed: D71.A, R121.1
unnamed: D72.A, R122.1
unnamed: R123.2, U41.5
unnamed: D73.C, R124.2
unnamed: R124.1, U41.1
unnamed: C155.2, U43.XO, Y11.P$2
unnamed: C156.2, U43.XI, Y11.P$1
unnamed: D77.A, R126.1
unnamed: D76.A, R125.1
unnamed: D78.A, R133.1
unnamed: D79.A, R134.1
unnamed: R135.2, U45.5
unnamed: D80.C, R136.2
unnamed: R136.1, U45.1
unnamed: C170.2, U47.XO, Y12.P$2
unnamed: C171.2, U47.XI, Y12.P$1
unnamed: D84.A, R138.1
unnamed: D83.A, R137.1
unnamed: D85.A, R145.1
unnamed: D86.A, R146.1
unnamed: R147.2, U49.5
unnamed: D87.C, R148.2
unnamed: R148.1, U49.1
unnamed: C185.2, U51.XO, Y13.P$2
unnamed: C186.2, U51.XI, Y13.P$1
unnamed: D91.A, R150.1
unnamed: D90.A, R149.1
unnamed: D92.A, R157.1
unnamed: D93.A, R158.1
unnamed: R159.2, U53.5
unnamed: D94.C, R160.2
unnamed: R160.1, U53.1
unnamed: C200.2, U55.XO, Y14.P$2
unnamed: C201.2, U55.XI, Y14.P$1
unnamed: D98.A, R162.1
unnamed: D97.A, R161.1
unnamed: D99.A, R169.1
unnamed: D100.A, R170.1
unnamed: R171.2, U57.5
unnamed: D101.C, R172.2
unnamed: R172.1, U57.1
unnamed: C215.2, U59.XO, Y15.P$2
unnamed: C216.2, U59.XI, Y15.P$1
unnamed: D105.A, R174.1
unnamed: D104.A, R173.1
unnamed: D106.A, R181.1
unnamed: D107.A, R182.1
unnamed: R183.2, U61.5
unnamed: D108.C, R184.2
unnamed: R184.1, U61.1
unnamed: C230.2, U63.XO, Y16.P$2
unnamed: C231.2, U63.XI, Y16.P$1
unnamed: D112.A, R186.1
unnamed: D111.A, R185.1
PDMCLK: E1.4, U1.~D37
PDMCLK1: E2.4, U7.~D37
PDMCLK2: E3.4, U11.~D37
PDMCLK3: E4.4, U15.~D37
PDMCLK4: E5.4, U19.~D37
PDMCLK5: E6.4, U23.~D37
PDMCLK6: E7.4, U27.~D37
PDMCLK7: E8.4, U31.~D37
PDMCLK8: E9.4, U35.~D37
PDMCLK9: E10.4, U39.~D37
PDMCLK10: E11.4, U43.~D37
PDMCLK11: E12.4, U47.~D37
PDMCLK12: E13.4, U51.~D37
PDMCLK13: E14.4, U55.~D37
PDMCLK14: E15.4, U59.~D37
PDMCLK15: E16.4, U63.~D37
PDMDATA: E1.1, U1.D36
PDMDATA1: E2.1, U7.D36
PDMDATA2: E3.1, U11.D36
PDMDATA3: E4.1, U15.D36
PDMDATA4: E5.1, U19.D36
PDMDATA5: E6.1, U23.D36
PDMDATA6: E7.1, U27.D36
PDMDATA7: E8.1, U31.D36
PDMDATA8: E9.1, U35.D36
PDMDATA9: E10.1, U39.D36
PDMDATA10: E11.1, U43.D36
PDMDATA11: E12.1, U47.D36
PDMDATA12: E13.1, U51.D36
PDMDATA13: E14.1, U55.D36
PDMDATA14: E15.1, U59.D36
PDMDATA15: E16.1, U63.D36
RXI-0: D5.C, TP5.P$1, U1.RXI-0, U6.8
RXI-1: D13.C, TP7.P$1, U7.RXI-0, U8.8
RXI-2: D20.C, TP13.P$1, U11.RXI-0, U12.8
RXI-3: D27.C, TP19.P$1, U15.RXI-0, U16.8
RXI-4: D34.C, TP25.P$1, U19.RXI-0, U20.8
RXI-5: D41.C, TP31.P$1, U23.RXI-0, U24.8
RXI-6: D48.C, TP37.P$1, U27.RXI-0, U28.8
RXI-7: D55.C, TP43.P$1, U31.RXI-0, U32.8
RXI-8: D62.C, TP49.P$1, U35.RXI-0, U36.8
RXI-9: D69.C, TP55.P$1, U39.RXI-0, U40.8
RXI-10: D76.C, TP61.P$1, U43.RXI-0, U44.8
RXI-11: D83.C, TP67.P$1, U47.RXI-0, U48.8
RXI-12: D90.C, TP73.P$1, U51.RXI-0, U52.8
RXI-13: D97.C, TP79.P$1, U55.RXI-0, U56.8
RXI-14: D104.C, TP85.P$1, U59.RXI-0, U60.8
RXI-15: D111.C, TP91.P$1, U63.RXI-0, U64.8
SHLD: J10.SHLD1, J10.SHLD2, J10.SHLD3, J10.SHLD4, J10.SHLD5, J10.SHLD6, J10.SHLD7, J10.SHLD8
SHLD1: J22.SHLD1, J22.SHLD2, J22.SHLD3, J22.SHLD4, J22.SHLD5, J22.SHLD6, J22.SHLD7, J22.SHLD8
SHLD2: J34.SHLD1, J34.SHLD2, J34.SHLD3, J34.SHLD4, J34.SHLD5, J34.SHLD6, J34.SHLD7, J34.SHLD8
SHLD3: J46.SHLD1, J46.SHLD2, J46.SHLD3, J46.SHLD4, J46.SHLD5, J46.SHLD6, J46.SHLD7, J46.SHLD8
SHLD4: J58.SHLD1, J58.SHLD2, J58.SHLD3, J58.SHLD4, J58.SHLD5, J58.SHLD6, J58.SHLD7, J58.SHLD8
SHLD5: J70.SHLD1, J70.SHLD2, J70.SHLD3, J70.SHLD4, J70.SHLD5, J70.SHLD6, J70.SHLD7, J70.SHLD8
SHLD6: J82.SHLD1, J82.SHLD2, J82.SHLD3, J82.SHLD4, J82.SHLD5, J82.SHLD6, J82.SHLD7, J82.SHLD8
SHLD7: J94.SHLD1, J94.SHLD2, J94.SHLD3, J94.SHLD4, J94.SHLD5, J94.SHLD6, J94.SHLD7, J94.SHLD8
SHLD8: J106.SHLD1, J106.SHLD2, J106.SHLD3, J106.SHLD4, J106.SHLD5, J106.SHLD6, J106.SHLD7, J106.SHLD8
SHLD9: J118.SHLD1, J118.SHLD2, J118.SHLD3, J118.SHLD4, J118.SHLD5, J118.SHLD6, J118.SHLD7, J118.SHLD8
SHLD10: J130.SHLD1, J130.SHLD2, J130.SHLD3, J130.SHLD4, J130.SHLD5, J130.SHLD6, J130.SHLD7, J130.SHLD8
SHLD11: J142.SHLD1, J142.SHLD2, J142.SHLD3, J142.SHLD4, J142.SHLD5, J142.SHLD6, J142.SHLD7, J142.SHLD8
SHLD12: J154.SHLD1, J154.SHLD2, J154.SHLD3, J154.SHLD4, J154.SHLD5, J154.SHLD6, J154.SHLD7, J154.SHLD8
SHLD13: J166.SHLD1, J166.SHLD2, J166.SHLD3, J166.SHLD4, J166.SHLD5, J166.SHLD6, J166.SHLD7, J166.SHLD8
SHLD14: J178.SHLD1, J178.SHLD2, J178.SHLD3, J178.SHLD4, J178.SHLD5, J178.SHLD6, J178.SHLD7, J178.SHLD8
SHLD15: J190.SHLD1, J190.SHLD2, J190.SHLD3, J190.SHLD4, J190.SHLD5, J190.SHLD6, J190.SHLD7, J190.SHLD8
SWDCK: J11.4, TP1.P$1, U1.SWDCK
SWDCK1: J23.4, TP9.P$1, U7.SWDCK
SWDCK2: J35.4, TP15.P$1, U11.SWDCK
SWDCK3: J47.4, TP21.P$1, U15.SWDCK
SWDCK4: J59.4, TP27.P$1, U19.SWDCK
SWDCK5: J71.4, TP33.P$1, U23.SWDCK
SWDCK6: J83.4, TP39.P$1, U27.SWDCK
SWDCK7: J95.4, TP45.P$1, U31.SWDCK
SWDCK8: J107.4, TP51.P$1, U35.SWDCK
SWDCK9: J119.4, TP57.P$1, U39.SWDCK
SWDCK10: J131.4, TP63.P$1, U43.SWDCK
SWDCK11: J143.4, TP69.P$1, U47.SWDCK
SWDCK12: J155.4, TP75.P$1, U51.SWDCK
SWDCK13: J167.4, TP81.P$1, U55.SWDCK
SWDCK14: J179.4, TP87.P$1, U59.SWDCK
SWDCK15: J191.4, TP93.P$1, U63.SWDCK
SWDIO: J11.2, TP2.P$1, U1.SWDIO
SWDIO1: J23.2, TP10.P$1, U7.SWDIO
SWDIO2: J35.2, TP16.P$1, U11.SWDIO
SWDIO3: J47.2, TP22.P$1, U15.SWDIO
SWDIO4: J59.2, TP28.P$1, U19.SWDIO
SWDIO5: J71.2, TP34.P$1, U23.SWDIO
SWDIO6: J83.2, TP40.P$1, U27.SWDIO
SWDIO7: J95.2, TP46.P$1, U31.SWDIO
SWDIO8: J107.2, TP52.P$1, U35.SWDIO
SWDIO9: J119.2, TP58.P$1, U39.SWDIO
SWDIO10: J131.2, TP64.P$1, U43.SWDIO
SWDIO11: J143.2, TP70.P$1, U47.SWDIO
SWDIO12: J155.2, TP76.P$1, U51.SWDIO
SWDIO13: J167.2, TP82.P$1, U55.SWDIO
SWDIO14: J179.2, TP88.P$1, U59.SWDIO
SWDIO15: J191.2, TP94.P$1, U63.SWDIO
TXO-0: D7.C, TP6.P$1, U1.TXO-0, U6.9
TXO-1: D14.C, TP8.P$1, U7.TXO-0, U8.9
TXO-2: D21.C, TP14.P$1, U11.TXO-0, U12.9
TXO-3: D28.C, TP20.P$1, U15.TXO-0, U16.9
TXO-4: D35.C, TP26.P$1, U19.TXO-0, U20.9
TXO-5: D42.C, TP32.P$1, U23.TXO-0, U24.9
TXO-6: D49.C, TP38.P$1, U27.TXO-0, U28.9
TXO-7: D56.C, TP44.P$1, U31.TXO-0, U32.9
TXO-8: D63.C, TP50.P$1, U35.TXO-0, U36.9
TXO-9: D70.C, TP56.P$1, U39.TXO-0, U40.9
TXO-10: D77.C, TP62.P$1, U43.TXO-0, U44.9
TXO-11: D84.C, TP68.P$1, U47.TXO-0, U48.9
TXO-12: D91.C, TP74.P$1, U51.TXO-0, U52.9
TXO-13: D98.C, TP80.P$1, U55.TXO-0, U56.9
TXO-14: D105.C, TP86.P$1, U59.TXO-0, U60.9
TXO-15: D112.C, TP92.P$1, U63.TXO-0, U64.9
VIN: C8.1, D3.C, D4.C, J2.12, R1.2, U3.1
VIN1: C4.1, D11.C, D12.C, J8.12, R24.2, U5.1
VIN2: C33.1, D18.C, D19.C, J26.12, R36.2, U10.1
VIN3: C48.1, D25.C, D26.C, J38.12, R48.2, U14.1
VIN4: C63.1, D32.C, D33.C, J50.12, R60.2, U18.1
VIN5: C78.1, D39.C, D40.C, J62.12, R72.2, U22.1
VIN6: C93.1, D46.C, D47.C, J74.12, R84.2, U26.1
VIN7: C108.1, D53.C, D54.C, J86.12, R96.2, U30.1
VIN8: C123.1, D60.C, D61.C, J98.12, R108.2, U34.1
VIN9: C138.1, D67.C, D68.C, J110.12, R120.2, U38.1
VIN10: C153.1, D74.C, D75.C, J122.12, R132.2, U42.1
VIN11: C168.1, D81.C, D82.C, J134.12, R144.2, U46.1
VIN12: C183.1, D88.C, D89.C, J146.12, R156.2, U50.1
VIN13: C198.1, D95.C, D96.C, J158.12, R168.2, U54.1
VIN14: C213.1, D102.C, D103.C, J170.12, R180.2, U58.1
VIN15: C228.1, D109.C, D110.C, J182.12, R192.2, U62.1
VREG_EN: J4.1, R1.1, U3.3
VREG_EN1: J24.1, R24.1, U5.3
VREG_EN2: J36.1, R36.1, U10.3
VREG_EN3: J48.1, R48.1, U14.3
VREG_EN4: J60.1, R60.1, U18.3
VREG_EN5: J72.1, R72.1, U22.3
VREG_EN6: J84.1, R84.1, U26.3
VREG_EN7: J96.1, R96.1, U30.3
VREG_EN8: J108.1, R108.1, U34.3
VREG_EN9: J120.1, R120.1, U38.3
VREG_EN10: J132.1, R132.1, U42.3
VREG_EN11: J144.1, R144.1, U46.3
VREG_EN12: J156.1, R156.1, U50.3
VREG_EN13: J168.1, R168.1, U54.3
VREG_EN14: J180.1, R180.1, U58.3
VREG_EN15: J192.1, R192.1, U62.3
V_BATT: C6.1, D4.A, J1.2, J12.2, U2.3
V_BATT1: C3.1, D12.A, J17.2, J19.2, U4.3
V_BATT2: C32.1, D19.A, J29.2, J31.2, U9.3
V_BATT3: C47.1, D26.A, J41.2, J43.2, U13.3
V_BATT4: C62.1, D33.A, J53.2, J55.2, U17.3
V_BATT5: C77.1, D40.A, J65.2, J67.2, U21.3
V_BATT6: C92.1, D47.A, J77.2, J79.2, U25.3
V_BATT7: C107.1, D54.A, J89.2, J91.2, U29.3
V_BATT8: C122.1, D61.A, J101.2, J103.2, U33.3
V_BATT9: C137.1, D68.A, J113.2, J115.2, U37.3
V_BATT10: C152.1, D75.A, J125.2, J127.2, U41.3
V_BATT11: C167.1, D82.A, J137.2, J139.2, U45.3
V_BATT12: C182.1, D89.A, J149.2, J151.2, U49.3
V_BATT13: C197.1, D96.A, J161.2, J163.2, U53.3
V_BATT14: C212.1, D103.A, J173.2, J175.2, U57.3
V_BATT15: C227.1, D110.A, J185.2, J187.2, U61.3
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
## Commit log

2019-07-01 Add TPs for I2C lines going to Qwiic connector.
2019-07-01 Rename to RedBoard
2019-07-03 Changed silk around PSWC PTH.
2019-07-03 Adding production panels
2019-07-03 Add OSHW logo
2022-11-05 Update README.md
    image link broken so updating from product page
2026-03-07 Add 3D models
2026-03-12 updated model with button and qwiic connector

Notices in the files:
parts and their libraries:
SparkFun-Aesthetics: Licensing: Creative Commons ShareAlike 4.0 International - https://creativecommons.org/licenses/by-sa/4.0
